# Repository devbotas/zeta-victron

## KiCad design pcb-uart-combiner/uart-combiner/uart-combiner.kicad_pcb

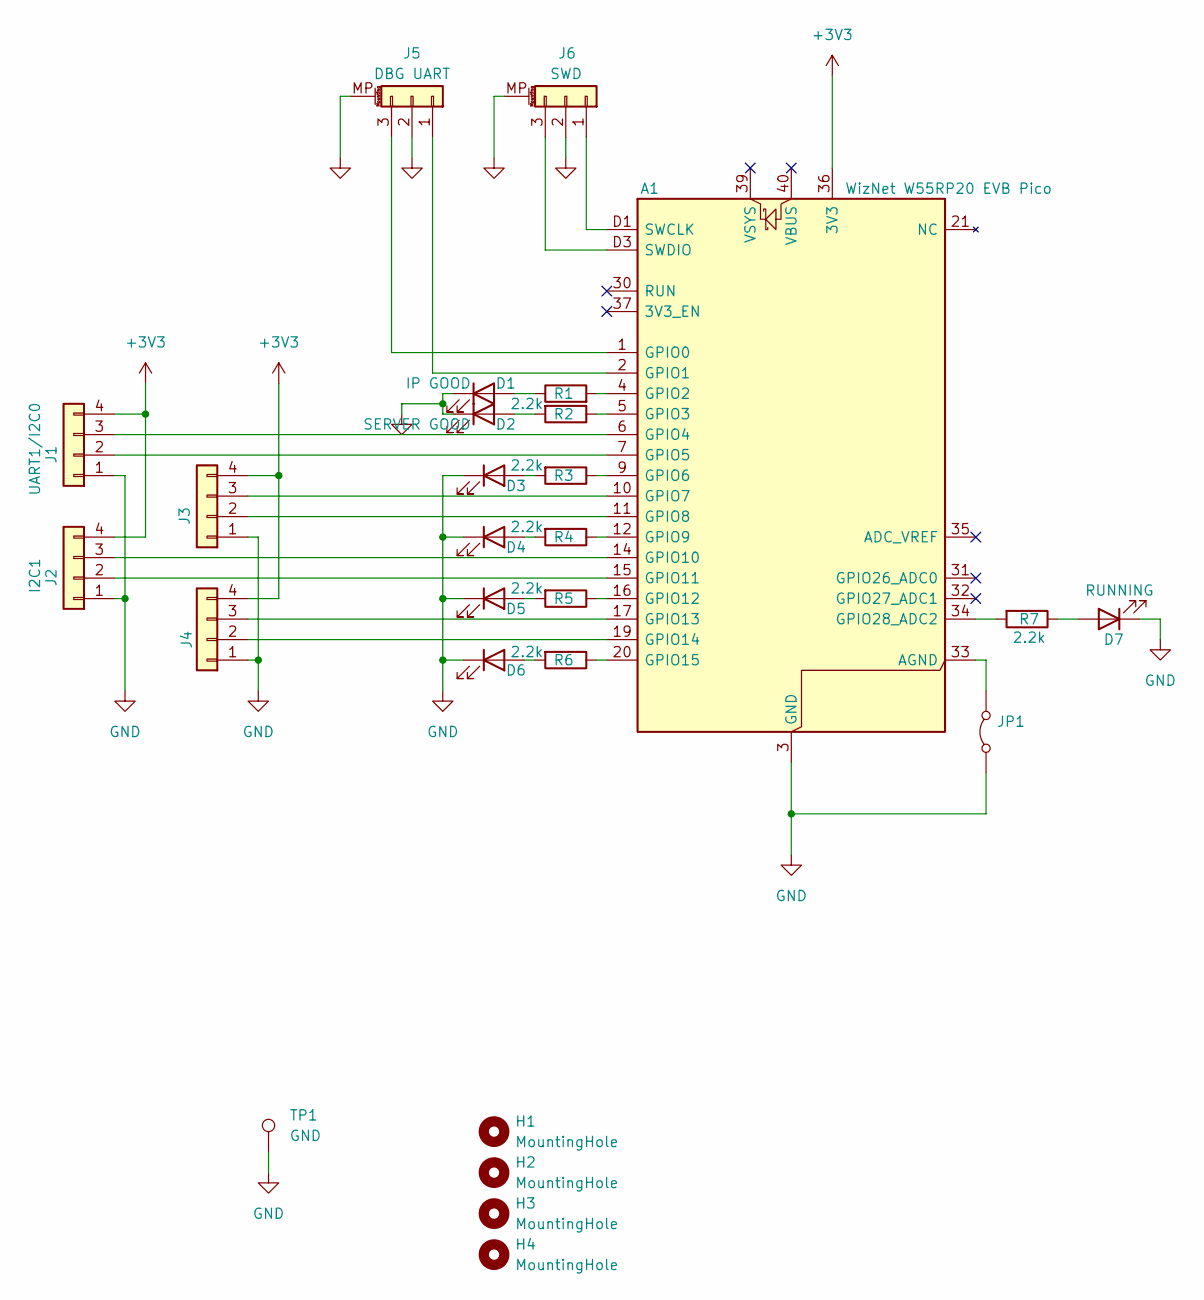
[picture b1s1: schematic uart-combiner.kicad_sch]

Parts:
A1: WizNet W55RP20 EVB Pico; WizNet_W55RP20_EVB_Pico
D1: IP GOOD; D_0603_1608Metric
D2: SERVER GOOD; D_0603_1608Metric
D3, D4, D5, D6: D_0603_1608Metric
D7: RUNNING; D_0603_1608Metric
H1, H2, H3, H4: MountingHole; MountingHole_3.2mm_M3_NoCopper
J1: UART1/I2C0; JST_PH_B4B-PH-K_1x04_P2.00mm_Vertical
J2: I2C1; JST_PH_B4B-PH-K_1x04_P2.00mm_Vertical
J3, J4: Conn_01x03; JST_PH_B4B-PH-K_1x04_P2.00mm_Vertical
J5: DBG UART; JST_SH_BM03B-SRSS-TB_1x03-1MP_P1.00mm_Vertical
J6: SWD; JST_SH_BM03B-SRSS-TB_1x03-1MP_P1.00mm_Vertical
JP1: Jumper_2_Bridged; SolderJumper-2_P1.3mm_Bridged_RoundedPad1.0x1.5mm
R1, R2, R3, R4, R5, R6, R7: 2.2k; R_0603_1608Metric
TP1: GND; TestPoint_Keystone_5019_Miniature

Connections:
+3V3: A1.36 (3V3), J1.4, J2.4, J3.4, J4.4
GND: A1.3 (GND), A1.8 (GND), A1.13 (GND), A1.18 (GND), A1.23 (GND), A1.28 (GND), A1.38 (GND), A1.D2 (GND), D1.1 (K), D2.1 (K), D3.1 (K), D4.1 (K), D5.1 (K), D6.1 (K), D7.1 (K), J1.1, J2.1, J3.1, J4.1, J5.2, J5.MP (MountPin), J6.2, J6.MP (MountPin), JP1.1 (A), TP1.1 (1_1)
unnamed: A1.33 (AGND), JP1.2 (B)
unnamed: A1.1 (GPIO0), J5.3
unnamed: A1.2 (GPIO1), J5.1
unnamed: A1.4 (GPIO2), R1.2
unnamed: A1.5 (GPIO3), R2.1
unnamed: A1.6 (GPIO4), J1.3
unnamed: A1.7 (GPIO5), J1.2
unnamed: A1.9 (GPIO6), R3.1
unnamed: A1.10 (GPIO7), J3.3
unnamed: A1.11 (GPIO8), J3.2
unnamed: A1.12 (GPIO9), R4.1
unnamed: A1.14 (GPIO10), J2.3
unnamed: A1.15 (GPIO11), J2.2
unnamed: A1.16 (GPIO12), R5.1
unnamed: A1.17 (GPIO13), J4.3
unnamed: A1.19 (GPIO14), J4.2
unnamed: A1.20 (GPIO15), R6.1
unnamed: A1.34 (GPIO28_ADC2), R7.2
unnamed: A1.D1 (SWCLK), J6.1
unnamed: A1.D3 (SWDIO), J6.3
unnamed: D1.2 (A), R1.1
unnamed: D2.2 (A), R2.2
unnamed: D3.2 (A), R3.2
unnamed: D4.2 (A), R4.2
unnamed: D5.2 (A), R5.2
unnamed: D6.2 (A), R6.2
unnamed: D7.2 (A), R7.1

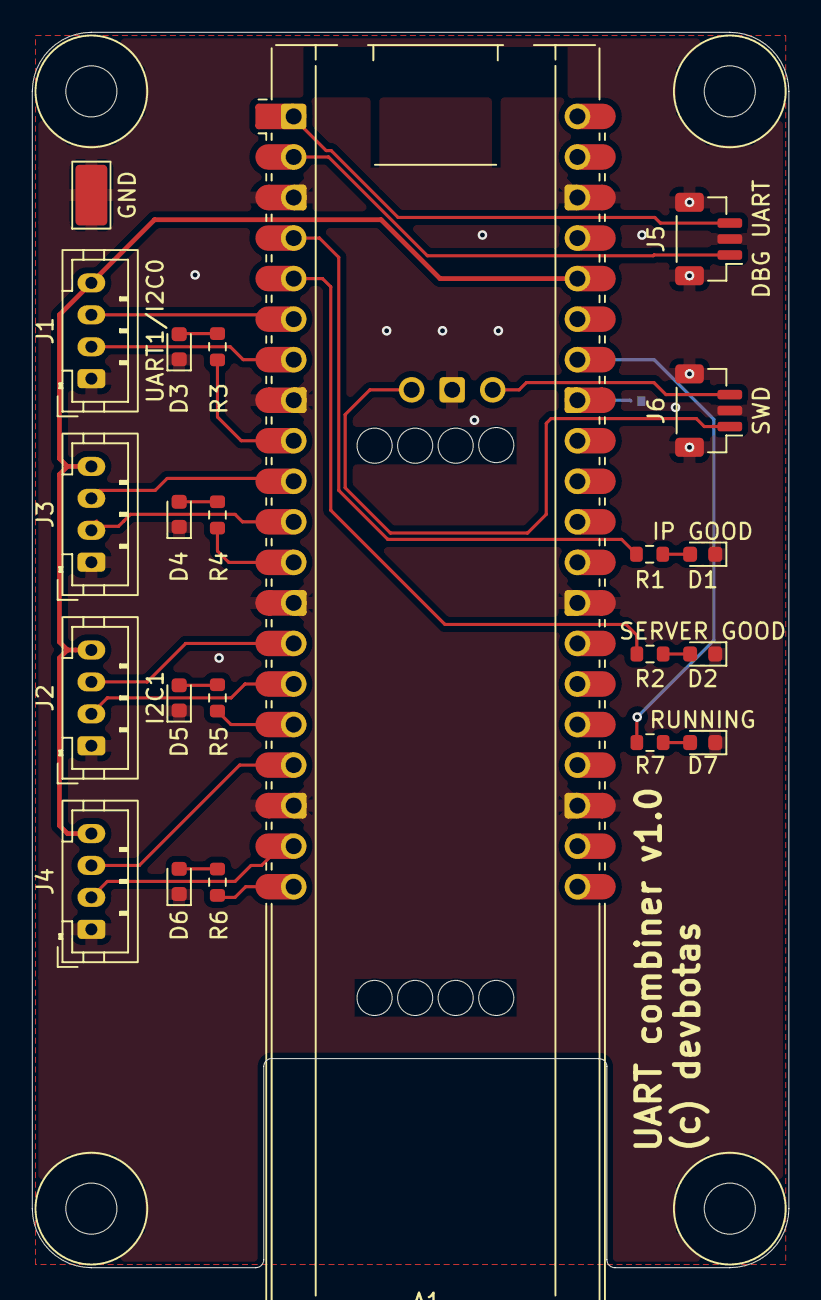
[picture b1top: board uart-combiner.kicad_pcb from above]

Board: 2 copper layers, 47.4 x 77.4 mm, 27 parts (1 on the bottom side), 29 nets.

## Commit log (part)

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2026-06-15 Fixing typo in folder.
2026-06-15 Splitting server side files for easier maintenance.
2026-06-16 Spawning holey boards into existence.
2026-06-22 Adding a working Arduino sketch on Wiznet Ethernet RP2040.
2026-06-23 Live debugging.
2026-06-24 Updating holey boards.
2026-06-29 Ignoring backup folders.
2026-06-29 Working on MPPT serail monitor. Basic validation is done. Need a proper PCB.
2026-06-30 Working on MPPT combiner.
2026-06-30 V1 mostly done.
